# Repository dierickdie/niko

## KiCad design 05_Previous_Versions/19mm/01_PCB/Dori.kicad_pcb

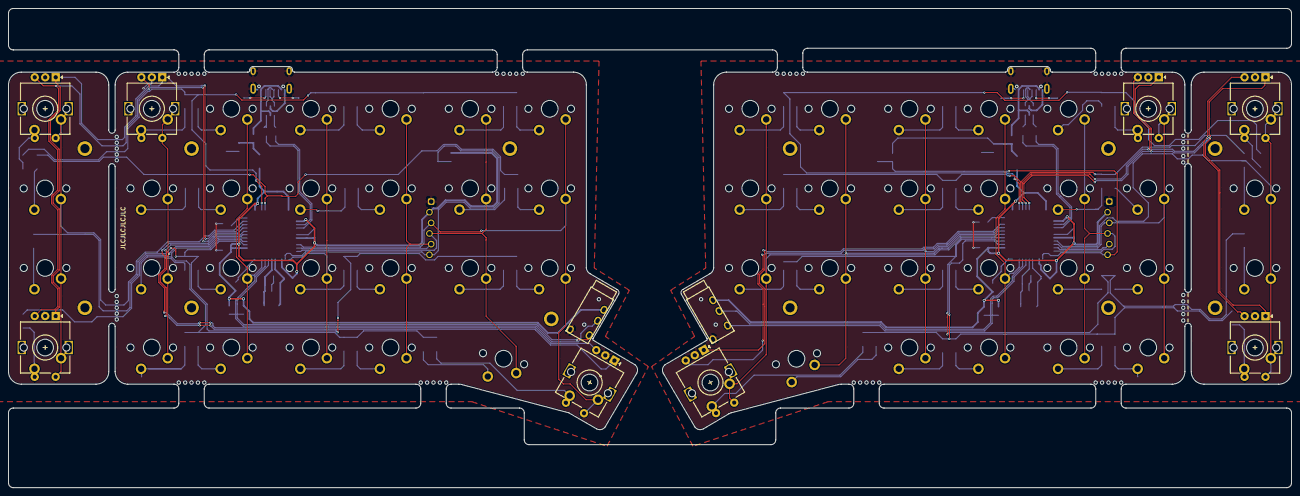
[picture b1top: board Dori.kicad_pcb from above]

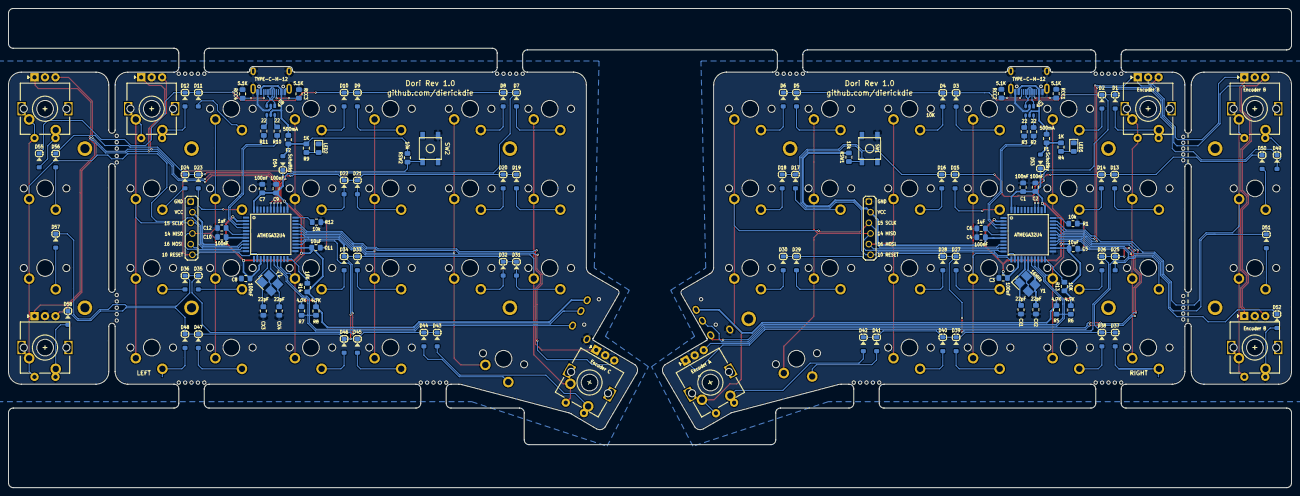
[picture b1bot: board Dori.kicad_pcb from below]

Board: 2 copper layers, 306.3 x 114.4 mm, 200 parts (111 on the bottom side), 129 nets.

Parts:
C1, C2, C3, C4, C7, C8, C9, C10: 100nF; C_0805_2012Metric_Pad1.15x1.40mm_HandSolder
C5, C11: 10uF; C_0805_2012Metric_Pad1.15x1.40mm_HandSolder
C6, C12: 1uF; C_0805_2012Metric_Pad1.15x1.40mm_HandSolder
CX1, CX2, CX3, CX4: 22pF; C_0805_2012Metric_Pad1.15x1.40mm_HandSolder
D1, D2, D3, D4, D5, D6, D7, D8, D9, D10, D11, D12, D13, D14, D15, D16, D17, D18, D19, D20, D21, D22, D23, D24, D25, D26, D27, D28, D29, D30, D31, D32, D33, D34, D35, D36, D37, D38, D39, D40, D41, D42, D43, D44, D45, D46, D47, D48, D49, D50, D51, D52, D55, D56, D57, D58: D; D_SOD-123_modified
D53, D54: Schottky; D_SOD-123_modified
F1, F2: 500mA; Fuse_0805_2012Metric_Pad1.15x1.40mm_HandSolder
H1, H2, H3, H4, H5, H6, H7, H8, H9, H10, H11, H12: MountingHole; Generic-Mounthole
J1, J5: TYPE-C-31-M12_13; TYPE-C-31-M-12
J2, J6: AVR-ISP-6_mod; PIN_HEADER_1x6_OFFSET
J3, J4: 4PIN; TRRS-PJ-320A
K1, K2, K3, K4, K5, K6, K7, K8, K9, K10, K11, K12, K13, K14, K15, K16, K17, K18, K19, K20, K21, K22, K23, K24, K25, K26, K27, K28, K29, K30, K31, K32, K33, K34, K35, K36, K37, K38, K39, K40, K41, K42, K43, K44, K45, K46, K47, K48, K49, K50, K51, K52, K53, K54, K55, K56: KEYSW; MX100
LED1, LED2: LED; LED_0805_2012Metric_Pad1.15x1.40mm_HandSolder
R1, R12: 10k; R_0805_2012Metric_Pad1.15x1.40mm_HandSolder
R2, R3, R10, R11: 22; R_0805_2012Metric_Pad1.15x1.40mm_HandSolder
R4, R9: 1K; R_0805_2012Metric_Pad1.15x1.40mm_HandSolder
R5, R6, R7, R8: 4.7K; R_0805_2012Metric_Pad1.15x1.40mm_HandSolder
R13, R14: 10K; R_0805_2012Metric_Pad1.15x1.40mm_HandSolder
RCC1, RCC2, RCC3, RCC4: 5.1K; R_0805_2012Metric_Pad1.15x1.40mm_HandSolder
RSW1, RSW2: 10k; R_0805_2012Metric_Pad1.15x1.40mm_HandSolder
SW1, SW2: SW_PUSH; SKQG-1155865
SW3, SW4, SW5, SW6, SW7, SW8, SW9, SW10: Rotary_Encoder_Switch; RotaryEncoder_EC11
U1, U12: ATMEGA32U4; ATMEGA32U4-AU
U2, U4, U5, U6, U7, U9, U10, U11, U13, U14, U15, U16: HOLE; MouseBite_IPC7351
U3, U8: USBLC6-2SC6; SOT-23-6
Y1, Y2: 16MHz; Crystal_SMD_3225-4Pin_3.2x2.5mm_HandSoldering

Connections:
+5V: D53.2, F1.1, R4.2
+5VA: D54.2, F2.1, R9.2, RSW2.2
D+BUSa: J1.A6, J1.B6, U3.3
D+BUSb: J5.A6, J5.B6, U8.3
D+a: R3.2, U3.4
D+b: R11.2, U8.4
D-BUSa: J1.A7, J1.B7, U3.1
D-BUSb: J5.A7, J5.B7, U8.1
D-a: R2.2, U3.6
D-b: R10.2, U8.6
Enc0a: SW8.A, U1.28
Enc0b: SW8.B, U1.29
Enc1a: SW3.A, SW4.A, SW10.A, U1.31
Enc1b: SW3.B, SW4.B, SW10.B, U1.30
Enc2a: SW9.A, U12.31
Enc2b: SW9.B, U12.30
Enc3a: SW5.A, SW6.A, SW7.A, U12.39
Enc3b: SW5.B, SW6.B, SW7.B, U12.38
GND: C1.2, C2.2, C3.2, C4.2, C5.2, C6.2, CX1.2, CX2.2, J1.A1, J1.B1, J1.S, J2.6, J3.1, LED1.1, R1.1, RCC1.1, RCC2.1, SW1.1, SW3.C, SW4.C, SW8.C, SW10.C, U1.5, U1.15, U1.23, U1.35, U1.43, U3.2, Y1.2, Y1.4
GNDA: C7.2, C8.2, C9.2, C10.2, C11.2, C12.2, CX3.2, CX4.2, J4.1, J5.A1, J5.B1, J5.S, J6.6, LED2.1, R12.1, RCC3.1, RCC4.1, SW2.1, SW6.C, SW7.C, SW9.C, U8.2, U12.5, U12.15, U12.23, U12.35, U12.43, Y2.2, Y2.4
HDETECT: R13.2, U1.22
HDETECTb: R14.2, U12.22
ISP_RSTa: J2.1, RSW1.1, SW1.2, U1.13
ISP_RSTb: J6.1, RSW2.1, SW2.2, U12.13
MOSIb: J6.4, U12.10
unnamed: C6.1, U1.6
unnamed: C12.1, U12.6
unnamed: D1.2, K1.2, SW3.S1
unnamed: D2.2, K2.2
unnamed: D3.2, K3.2
unnamed: D4.2, K4.2
unnamed: D5.2, K5.2
unnamed: D6.2, K6.2
unnamed: D7.2, K7.2
unnamed: D8.2, K8.2
unnamed: D9.2, K9.2
unnamed: D10.2, K10.2
unnamed: D11.2, K11.2
unnamed: D12.2, K12.2, SW7.S1
unnamed: D13.2, K13.2
unnamed: D14.2, K14.2
unnamed: D15.2, K15.2
unnamed: D16.2, K16.2
unnamed: D17.2, K17.2
unnamed: D18.2, K18.2
unnamed: D19.2, K19.2
unnamed: D20.2, K20.2
unnamed: D21.2, K21.2
unnamed: D22.2, K22.2
unnamed: D23.2, K23.2
unnamed: D24.2, K24.2
unnamed: D25.2, K25.2
unnamed: D26.2, K26.2
unnamed: D27.2, K27.2
unnamed: D28.2, K28.2
unnamed: D29.2, K29.2
unnamed: D30.2, K30.2
unnamed: D31.2, K31.2
unnamed: D32.2, K32.2
unnamed: D33.2, K33.2
unnamed: D34.2, K34.2
unnamed: D35.2, K35.2
unnamed: D36.2, K36.2
unnamed: D37.2, K37.2
unnamed: D38.2, K38.2
unnamed: D39.2, K39.2
unnamed: D40.2, K40.2
unnamed: D41.2, K41.2
unnamed: D42.2, K42.2, SW8.S1
unnamed: D43.2, K43.2, SW9.S1
unnamed: D44.2, K44.2
unnamed: D45.2, K45.2
unnamed: D46.2, K46.2
unnamed: D47.2, K47.2
unnamed: D48.2, K48.2
unnamed: D49.2, K49.2, SW4.S1
unnamed: D50.2, K50.2
unnamed: D51.2, K51.2
unnamed: D52.2, K52.2, SW10.S1
unnamed: D55.2, K53.2, SW5.S1
unnamed: D56.2, K54.2
unnamed: D57.2, K55.2
unnamed: D58.2, K56.2, SW6.S1
unnamed: J1.A5, RCC1.2
unnamed: J1.B5, RCC2.2
unnamed: J5.A5, RCC3.2
unnamed: J5.B5, RCC4.2
unnamed: LED1.2, R4.1
unnamed: LED2.2, R9.1
unnamed: R1.2, U1.33
unnamed: R2.1, U1.3
unnamed: R3.1, U1.4
unnamed: R10.1, U12.3
unnamed: R11.1, U12.4
unnamed: R12.2, U12.33
SCLa: J3.2, R5.2, U1.18
SCLb: J4.2, R7.2, U12.18
SDAa: J3.3, R6.2, U1.19
SDAb: J4.3, R8.2, U12.19
VBUSa: F1.2, J1.A4, J1.B4, U3.5
VBUSb: F2.2, J5.A4, J5.B4, U8.5
VCC: C1.1, C2.1, C3.1, C4.1, C5.1, D53.1, J2.2, J3.4, R5.1, R6.1, R13.1, RSW1.2, U1.2, U1.7, U1.14, U1.24, U1.34, U1.44
VDD: C7.1, C8.1, C9.1, C10.1, C11.1, D54.1, J4.4, J6.2, R7.1, R8.1, R14.1, U12.2, U12.7, U12.14, U12.24, U12.34, U12.44
XTAL1a: CX1.1, U1.16, Y1.1
XTAL1b: CX3.1, U12.16, Y2.1
XTAL2a: CX2.1, U1.17, Y1.3
XTAL2b: CX4.1, U12.17, Y2.3
col0a: K1.1, K13.1, K25.1, K37.1, SW3.S2, U1.27
col0b: K7.1, K19.1, K31.1, K43.1, SW9.S2, U12.27
col1a: K2.1, K14.1, K26.1, K38.1, U1.20
col1b: K8.1, K20.1, K32.1, K44.1, U12.28
col2a: K3.1, K15.1, K27.1, K39.1, U1.12
col2b: K9.1, K21.1, K33.1, K45.1, U12.29
col3a: J2.4, K4.1, K16.1, K28.1, K40.1, U1.10
col3b: K10.1, K22.1, K34.1, K46.1, U12.20
col4a: J2.3, K5.1, K17.1, K29.1, K41.1, U1.11
col4b: J6.3, K11.1, K23.1, K35.1, K47.1, U12.11
col5a: J2.5, K6.1, K18.1, K30.1, K42.1, SW8.S2, U1.9
col5b: J6.5, K12.1, K24.1, K36.1, K48.1, SW7.S2, U12.9
col6a: K49.1, K50.1, K51.1, K52.1, SW4.S2, SW10.S2, U1.32
col6b: K53.1, K54.1, K55.1, K56.1, SW5.S2, SW6.S2, U12.8
row0a: D1.1, D2.1, D3.1, D4.1, D5.1, D6.1, D49.1, U1.36
row0b: D7.1, D8.1, D9.1, D10.1, D11.1, D12.1, D55.1, U12.36
row1a: D13.1, D14.1, D15.1, D16.1, D17.1, D18.1, D50.1, U1.37
row1b: D19.1, D20.1, D21.1, D22.1, D23.1, D24.1, D56.1, U12.37
row2a: D25.1, D26.1, D27.1, D28.1, D29.1, D30.1, D51.1, U1.25
row2b: D31.1, D32.1, D33.1, D34.1, D35.1, D36.1, D57.1, U12.26
row3a: D37.1, D38.1, D39.1, D40.1, D41.1, D42.1, D52.1, U1.26
row3b: D43.1, D44.1, D45.1, D46.1, D47.1, D48.1, D58.1, U12.25

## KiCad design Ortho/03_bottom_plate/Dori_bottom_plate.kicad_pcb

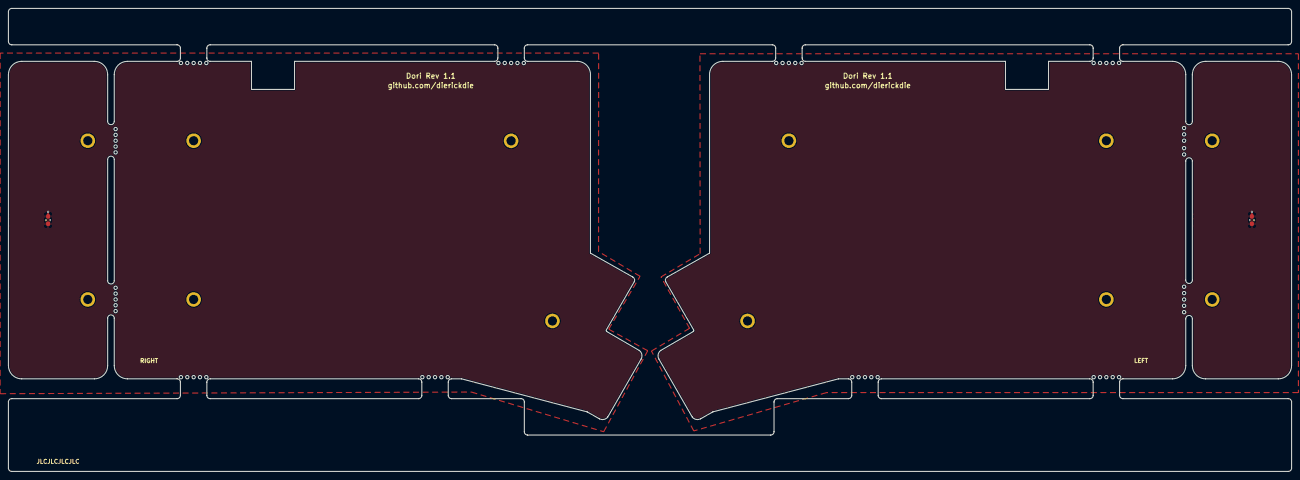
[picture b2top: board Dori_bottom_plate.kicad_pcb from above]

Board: 2 copper layers, 308.0 x 111.1 mm, 84 parts (1 on the bottom side), 2 nets.

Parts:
H1, H2, H3, H4, H5, H6, H7, H8, H9, H10, H11, H12: MountingHole; Generic-Mounthole
J1, J2: 4PIN; TRRS-PJ-320A
R1, R2: R_Small; R_0603_1608Metric_Pad1.05x0.95mm_HandSolder
U1, U2, U3, U4, U5, U6, U7, U8, U9, U10, U11, U12, U13, U14, U15, U16, U17, U18, U19, U20, U21, U22, U23, U24, U25, U26, U27, U28, U29, U30, U31, U32, U33, U34, U35, U36, U37, U38, U39, U40, U41, U42, U43, U44, U45, U46, U47, U48, U49, U50, U51, U52, U53, U54, U55, U56: HOLE; MX100_outline
U57, U58, U59, U60, U61, U62, U63, U64, U65, U66, U67, U68: HOLE; MouseBite_IPC7351

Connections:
GND: R1.1, R1.2
GNDA: R2.1, R2.2
